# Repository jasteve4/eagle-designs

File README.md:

# eagle-designs
designs for ncsu IEEE Robotics

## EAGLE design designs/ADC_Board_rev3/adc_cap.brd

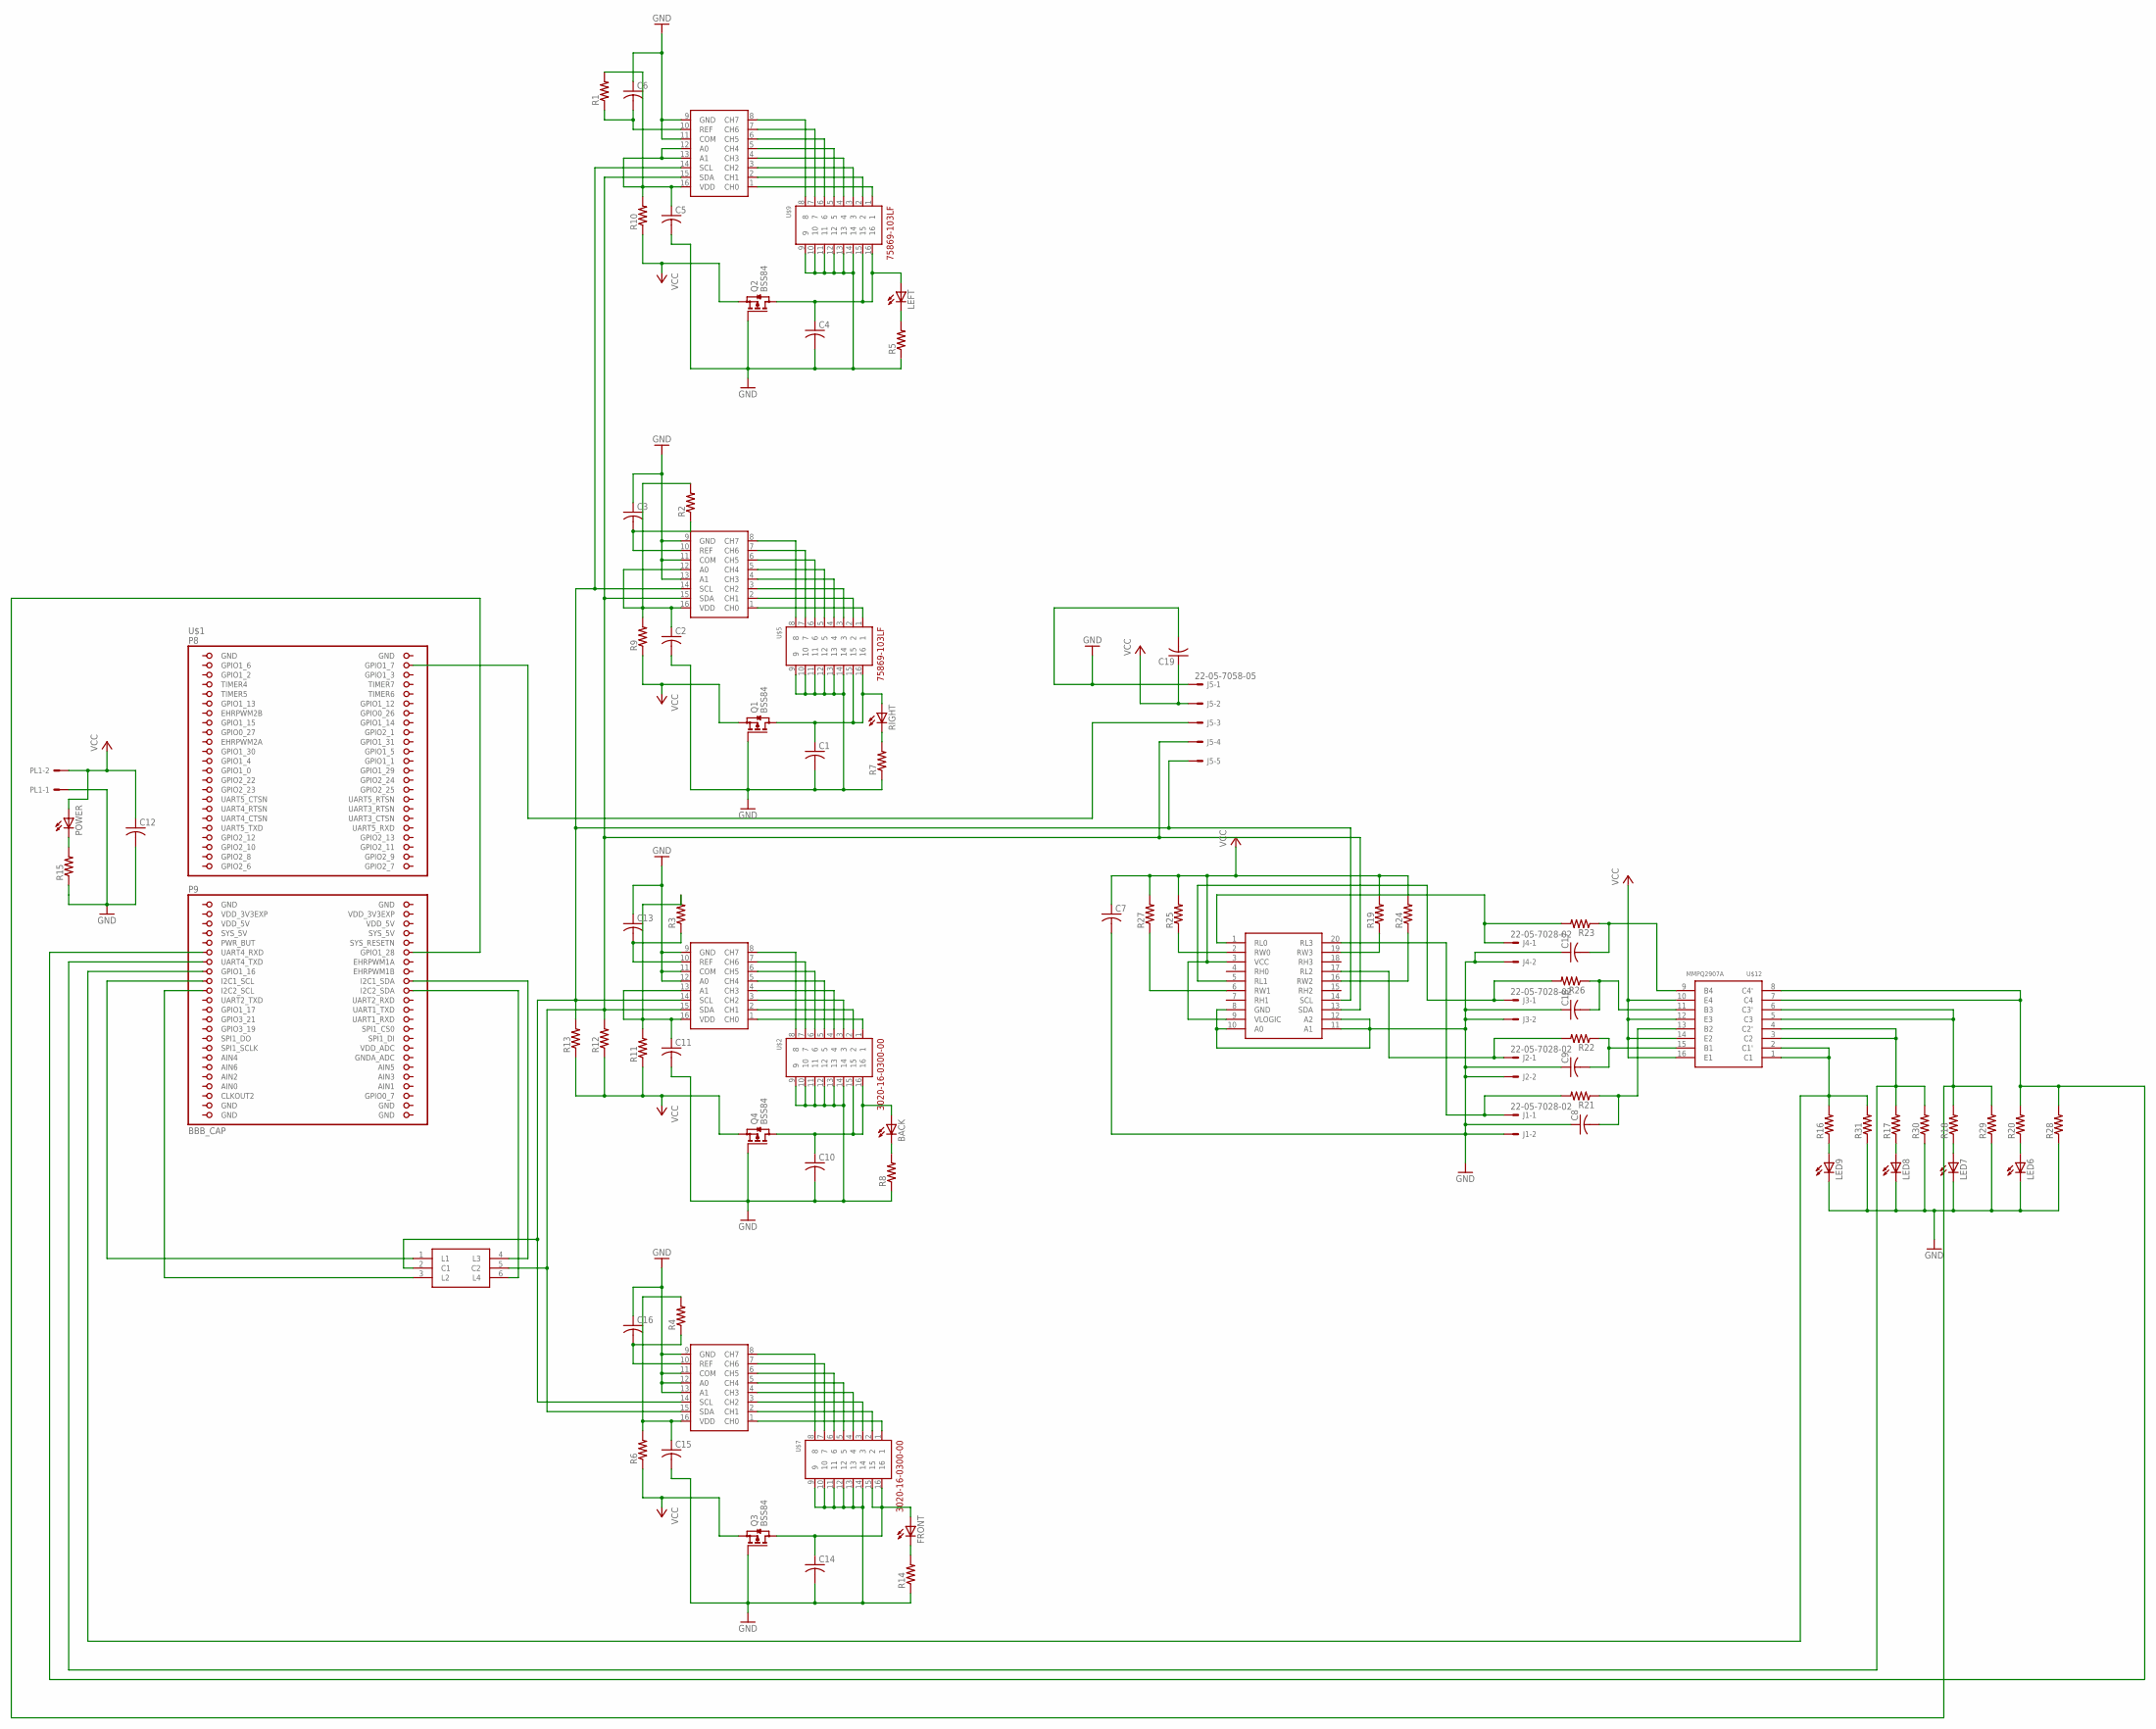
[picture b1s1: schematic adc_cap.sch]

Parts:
BACK: LEDSML1206; SML1206
C1, C2, C3, C4, C5, C6, C7, C8, C9, C10, C11, C13, C14, C15, C16, C17, C18, C19: C-USC1206K; C1206K
C12: C-USC0805; C0805
FRONT: LEDSML1206; SML1206
J1, J2, J3, J4: 22-05-7028-02; 7395-02
J5: 22-05-7058-05; 7395-05
LED6, LED7, LED8, LED9: LEDSML1206; SML1206
LEFT: LEDSML1206; SML1206
PL1: 555X-2H; 5569-2
POWER: LEDSML1206; SML1206
Q1, Q2, Q3, Q4: BSS84; SOT23
R1, R2, R3, R4, R5, R6, R7, R8, R9, R10, R11, R12, R13, R14, R15, R16, R17, R18, R19, R20, R21, R22, R23, R24, R25, R26, R27, R28, R29, R30, R31: R-US_R1206W; R1206W
RIGHT: LEDSML1206; SML1206
U$1: BBB_CAP; BBB
U$2, U$7: 3020-16-0300-00; 8X2_SMD_HEADER
U$3, U$4, U$6, U$8: ADS7830; ADC8_SD
U$5, U$9: 75869-103LF; 8X2_THROUGH_HOLE_HEADER
U$10: CAS-220TB; DPDT_DIP_SWITCH
U$11: ISL23348_SD; TSSOP-20
U$12: MMPQ2907A; SO1C-16

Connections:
AIN0: U$1.P9_39 (AIN0)
GND: C1.2, C2.2, C3.1, C4.2, C5.2, C6.1, C7.2, C8.1, C9.1, C10.2, C11.2, C12.2, C13.1, C14.2, C15.2, C16.1, C17.1, C18.1, C19.2, J1.2, J2.2, J3.2, J4.2, J5.1, LED6.C, LED7.C, LED8.C, LED9.C, PL1.1, Q1.1 (G), Q2.1 (G), Q3.1 (G), Q4.1 (G), R5.1, R7.1, R8.1, R14.1, R28.1, R29.1, R30.1, R31.1, U$1.P8_1 (GND), U$1.P8_2 (GND), U$1.P9_1 (GND), U$1.P9_2 (GND), U$1.P9_43 (GND), U$1.P9_44 (GND), U$1.P9_45 (GND), U$1.P9_46 (GND), U$2.9, U$2.10, U$2.11, U$2.12, U$2.13, U$2.14, U$3.9 (GND), U$3.11 (COM), U$3.12 (A0), U$4.9 (GND), U$4.11 (COM), U$4.13 (A1), U$5.9, U$5.10, U$5.11, U$5.12, U$5.13, U$5.14, U$6.9 (GND), U$6.11 (COM), U$7.9, U$7.10, U$7.11, U$7.12, U$7.13, U$7.14, U$8.9 (GND), U$8.11 (COM), U$8.12 (A0), U$8.13 (A1), U$9.9, U$9.10, U$9.11, U$9.12, U$9.13, U$9.14, U$11.8 (GND), U$11.10 (A0), U$11.11 (A1), U$11.12 (A2)
GND4: R15.1
unnamed: U$2.1, U$3.1 (CH0)
unnamed: J5.4, R12.2, U$3.15 (SDA), U$4.15 (SDA), U$6.15 (SDA), U$8.15 (SDA), U$10.5 (C2), U$11.13 (SDA)
unnamed: U$2.2, U$3.2 (CH1)
unnamed: U$2.3, U$3.3 (CH2)
unnamed: U$2.4, U$3.4 (CH3)
unnamed: U$2.5, U$3.5 (CH4)
unnamed: U$2.6, U$3.6 (CH5)
unnamed: U$2.7, U$3.7 (CH6)
unnamed: U$2.8, U$3.8 (CH7)
unnamed: U$1.P9_18 (I2C1_SDA), U$10.4 (L3)
unnamed: U$1.P9_20 (I2C2_SDA), U$10.6 (L4)
unnamed: C13.2, R3.1, U$3.10 (REF)
unnamed: J5.5, R13.2, U$3.14 (SCL), U$4.14 (SCL), U$6.14 (SCL), U$8.14 (SCL), U$10.2 (C1), U$11.14 (SCL)
unnamed: R19.1, U$11.19 (RW3)
unnamed: U$4.1 (CH0), U$5.1
unnamed: U$4.2 (CH1), U$5.2
unnamed: U$4.3 (CH2), U$5.3
unnamed: U$4.4 (CH3), U$5.4
unnamed: U$4.5 (CH4), U$5.5
unnamed: U$4.6 (CH5), U$5.6
unnamed: U$4.7 (CH6), U$5.7
unnamed: U$4.8 (CH7), U$5.8
unnamed: U$1.P9_17 (I2C1_SCL), U$10.1 (L1)
unnamed: U$1.P9_19 (I2C2_SCL), U$10.3 (L2)
unnamed: C11.1, R3.2, R11.2, U$3.13 (A1), U$3.16 (VDD)
unnamed: C3.2, R2.1, U$4.10 (REF)
unnamed: C4.1, LEFT.A, Q2.3 (D), U$9.15, U$9.16
unnamed: U$6.1 (CH0), U$9.1
unnamed: U$6.2 (CH1), U$9.2
unnamed: U$6.3 (CH2), U$9.3
unnamed: U$6.4 (CH3), U$9.4
unnamed: U$6.5 (CH4), U$9.5
unnamed: U$6.6 (CH5), U$9.6
unnamed: U$6.7 (CH6), U$9.7
unnamed: U$6.8 (CH7), U$9.8
unnamed: R24.1, U$11.16 (RW2)
unnamed: U$7.1, U$8.1 (CH0)
unnamed: C2.1, R2.2, R9.2, U$4.12 (A0), U$4.16 (VDD)
unnamed: C6.2, R1.1, U$6.10 (REF)
unnamed: R25.1, U$11.2 (RW0)
unnamed: U$7.2, U$8.2 (CH1)
unnamed: U$7.3, U$8.3 (CH2)
unnamed: U$7.4, U$8.4 (CH3)
unnamed: U$7.5, U$8.5 (CH4)
unnamed: U$7.6, U$8.6 (CH5)
unnamed: U$7.7, U$8.7 (CH6)
unnamed: U$7.8, U$8.8 (CH7)
unnamed: C5.1, R1.2, R10.2, U$6.12 (A0), U$6.13 (A1), U$6.16 (VDD)
unnamed: LEFT.C, R5.2
unnamed: R27.1, U$11.6 (RW1)
unnamed: C15.1, R4.2, R6.2, U$8.16 (VDD)
unnamed: C16.2, R4.1, U$8.10 (REF)
unnamed: C1.1, Q1.3 (D), RIGHT.A, U$5.15, U$5.16
unnamed: R7.2, RIGHT.C
unnamed: BACK.A, C10.1, Q4.3 (D), U$2.15, U$2.16
unnamed: BACK.C, R8.2
unnamed: C14.1, FRONT.A, Q3.3 (D), U$7.15, U$7.16
unnamed: FRONT.C, R14.2
unnamed: LED8.A, R17.1
unnamed: POWER.C, R15.2
unnamed: J4.1, R23.2, U$11.1 (RL0)
unnamed: J3.1, R26.2, U$11.5 (RL1)
unnamed: J2.1, R22.2, U$11.17 (RL2)
unnamed: J1.1, R21.2, U$11.20 (RL3)
unnamed: LED9.A, R16.1
unnamed: LED7.A, R18.1
unnamed: LED6.A, R20.1
unnamed: C17.2, R23.1, U$12.9 (B4)
unnamed: C18.2, R26.1, U$12.11 (B3)
unnamed: C9.2, R22.1, U$12.15 (B1)
unnamed: C8.2, R21.1, U$12.13 (B2)
unnamed: J5.3, U$1.P8_4 (GPIO1_7)
unnamed: R17.2, R30.2, U$1.P9_13 (UART4_TXD), U$12.3 (C2), U$12.4 (C2')
unnamed: R20.2, R28.2, U$1.P9_11 (UART4_RXD), U$12.7 (C4), U$12.8 (C4')
unnamed: R18.2, R29.2, U$1.P9_12 (GPIO1_28), U$12.5 (C3), U$12.6 (C3')
unnamed: R16.2, R31.2, U$1.P9_15 (GPIO1_16), U$12.1 (C1), U$12.2 (C1')
SYS_5V: U$1.P9_7 (SYS_5V)
VCC: C7.1, C12.1, C19.1, J5.2, PL1.2, POWER.A, Q1.2 (S), Q2.2 (S), Q3.2 (S), Q4.2 (S), R6.1, R9.1, R10.1, R11.1, R12.1, R13.1, R19.2, R24.2, R25.2, R27.2, U$11.3 (VCC), U$11.9 (VLOGIC), U$12.10 (E4), U$12.12 (E3), U$12.14 (E2), U$12.16 (E1)
VDD_3V3EXP: U$1.P9_3 (VDD_3V3EXP), U$1.P9_4 (VDD_3V3EXP)
VDD_5V: U$1.P9_5 (VDD_5V), U$1.P9_6 (VDD_5V)

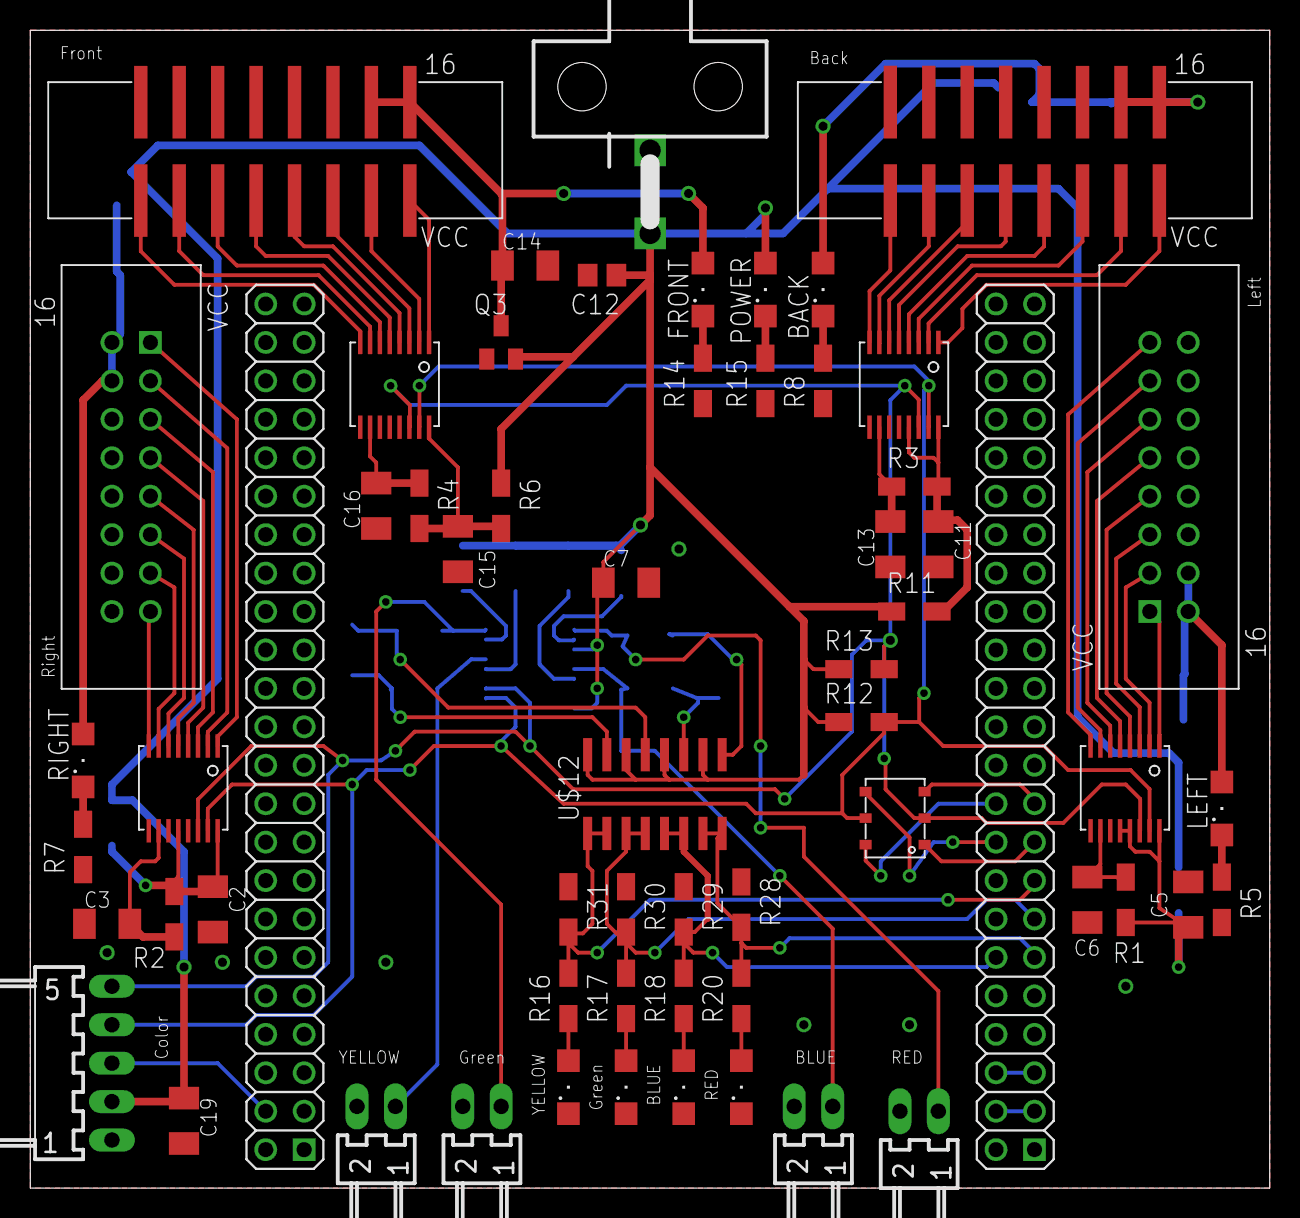
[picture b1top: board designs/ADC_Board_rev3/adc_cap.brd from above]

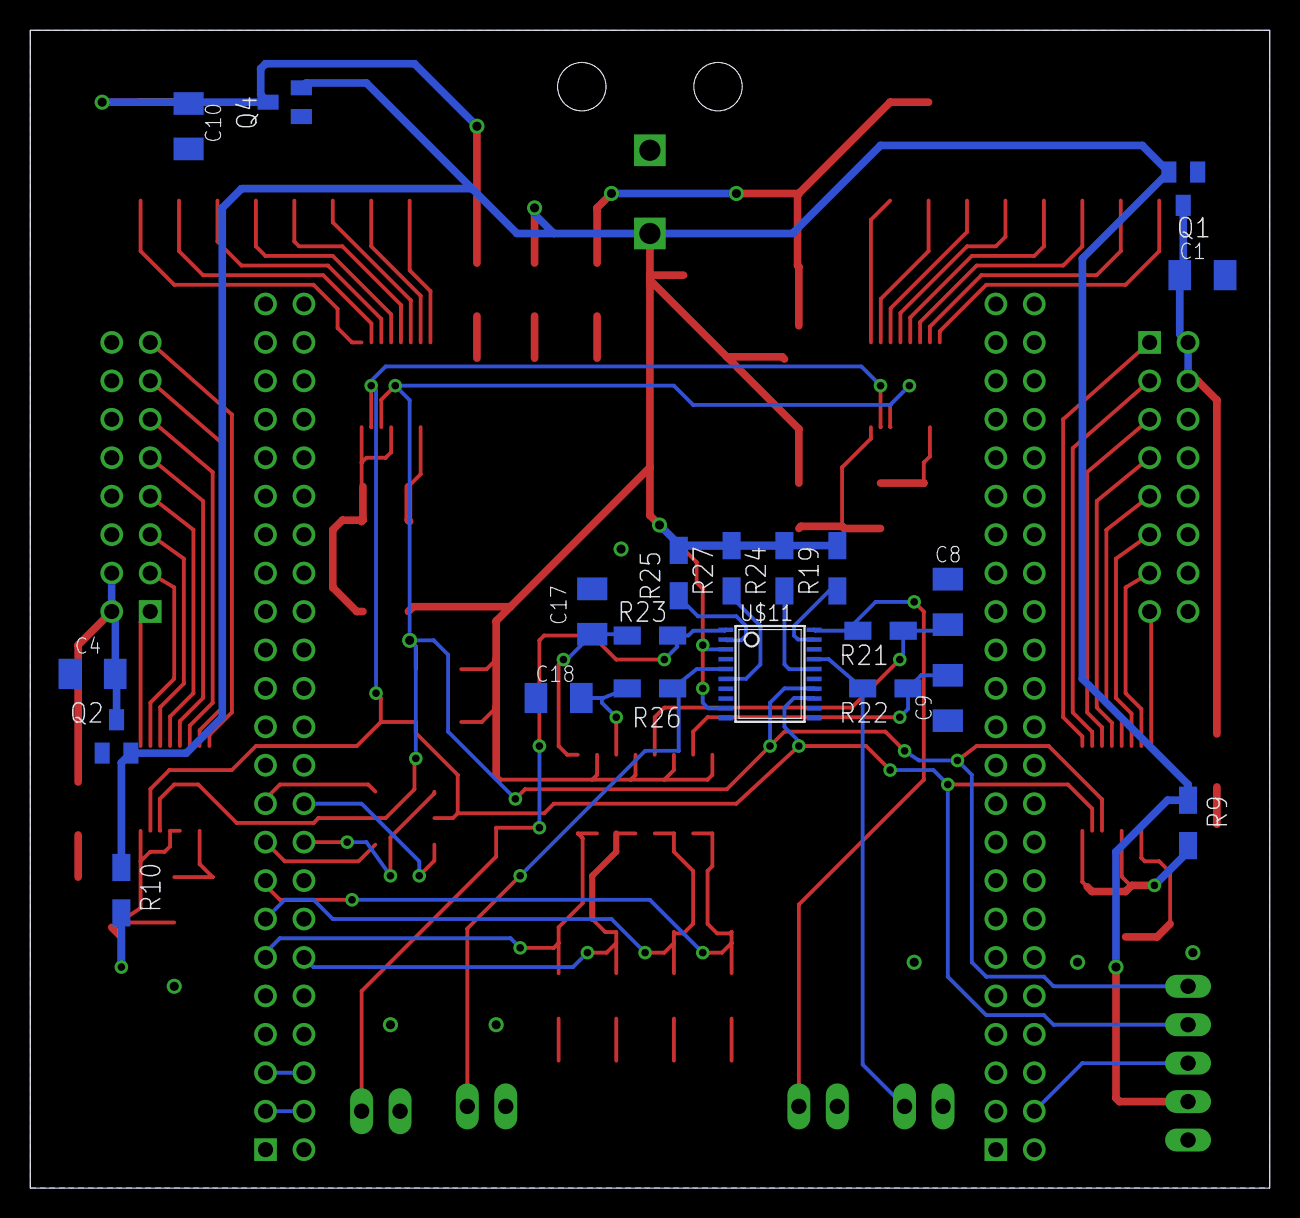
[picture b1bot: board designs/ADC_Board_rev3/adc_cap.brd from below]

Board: 2 copper layers, 81.9 x 76.5 mm, 81 parts (21 on the bottom side), 80 nets.

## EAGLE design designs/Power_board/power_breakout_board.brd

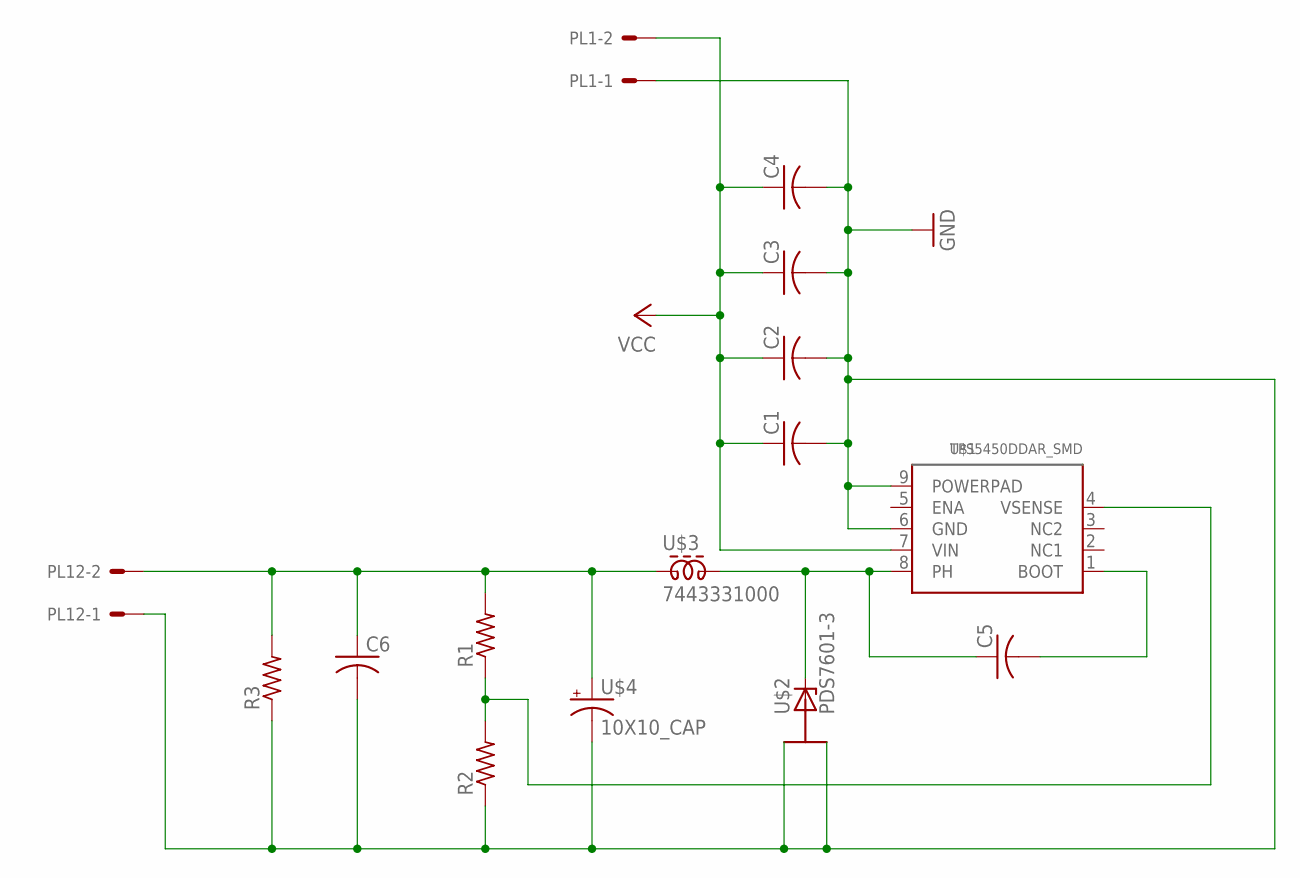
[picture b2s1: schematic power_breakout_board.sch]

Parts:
C1, C2, C3, C4, C6: C-USC1206K; C1206K
C5: C-USC0805K; C0805K
PL1, PL12: 555X-2H; 5569-2
R1, R2, R3: R-US_R1206; R1206
U$1: TPS5450DDAR_SMD; SO-POWERPAD
U$2: PDS7601-3; POWERDI-5_SMD
U$3: 7443331000; 7443331000_SMD
U$4: 10X10_CAP; 10X10_CAP_SMD

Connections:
GND: C1.2, C2.2, C3.2, C4.2, C6.2, PL1.1, PL12.1, R2.1, R3.1, U$1.6 (GND), U$1.9 (POWERPAD), U$2.LEFT, U$2.RIGHT, U$4.-
unnamed: C5.2, U$1.1 (BOOT)
unnamed: R1.1, R2.2, U$1.4 (VSENSE)
PH: C5.1, U$1.8 (PH), U$2.HEAT, U$3.P2 (2)
VCC: C1.1, C2.1, C3.1, C4.1, PL1.2, U$1.7 (VIN)
VOUT: C6.1, PL12.2, R1.2, R3.2, U$3.P1 (1), U$4.+

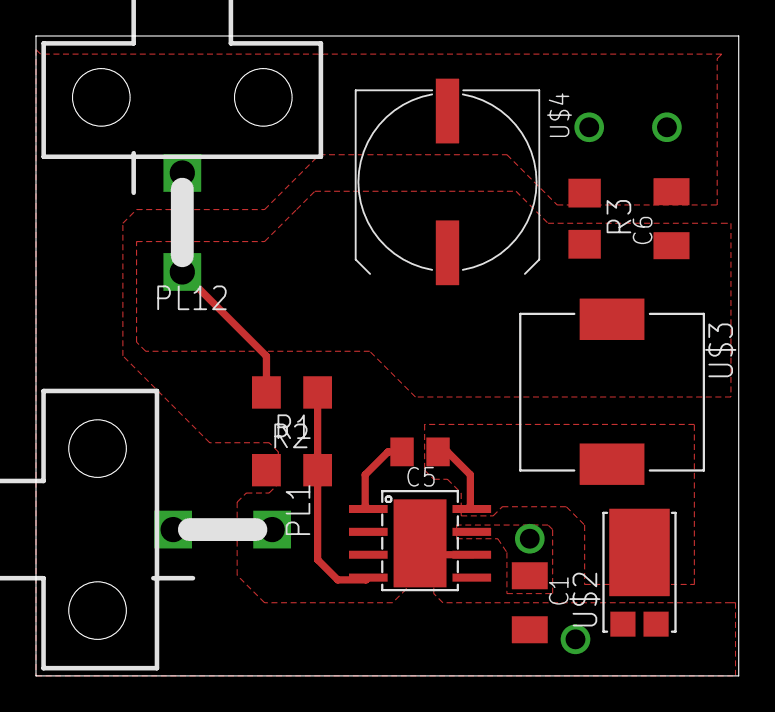
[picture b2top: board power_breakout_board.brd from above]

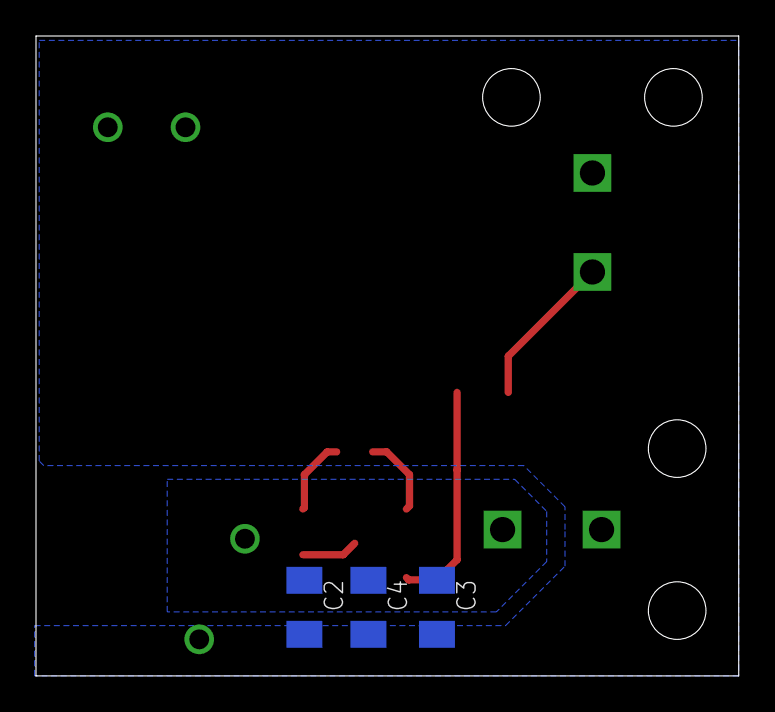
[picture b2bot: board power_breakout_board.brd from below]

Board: 2 copper layers, 39.0 x 35.5 mm, 15 parts (3 on the bottom side), 6 nets.

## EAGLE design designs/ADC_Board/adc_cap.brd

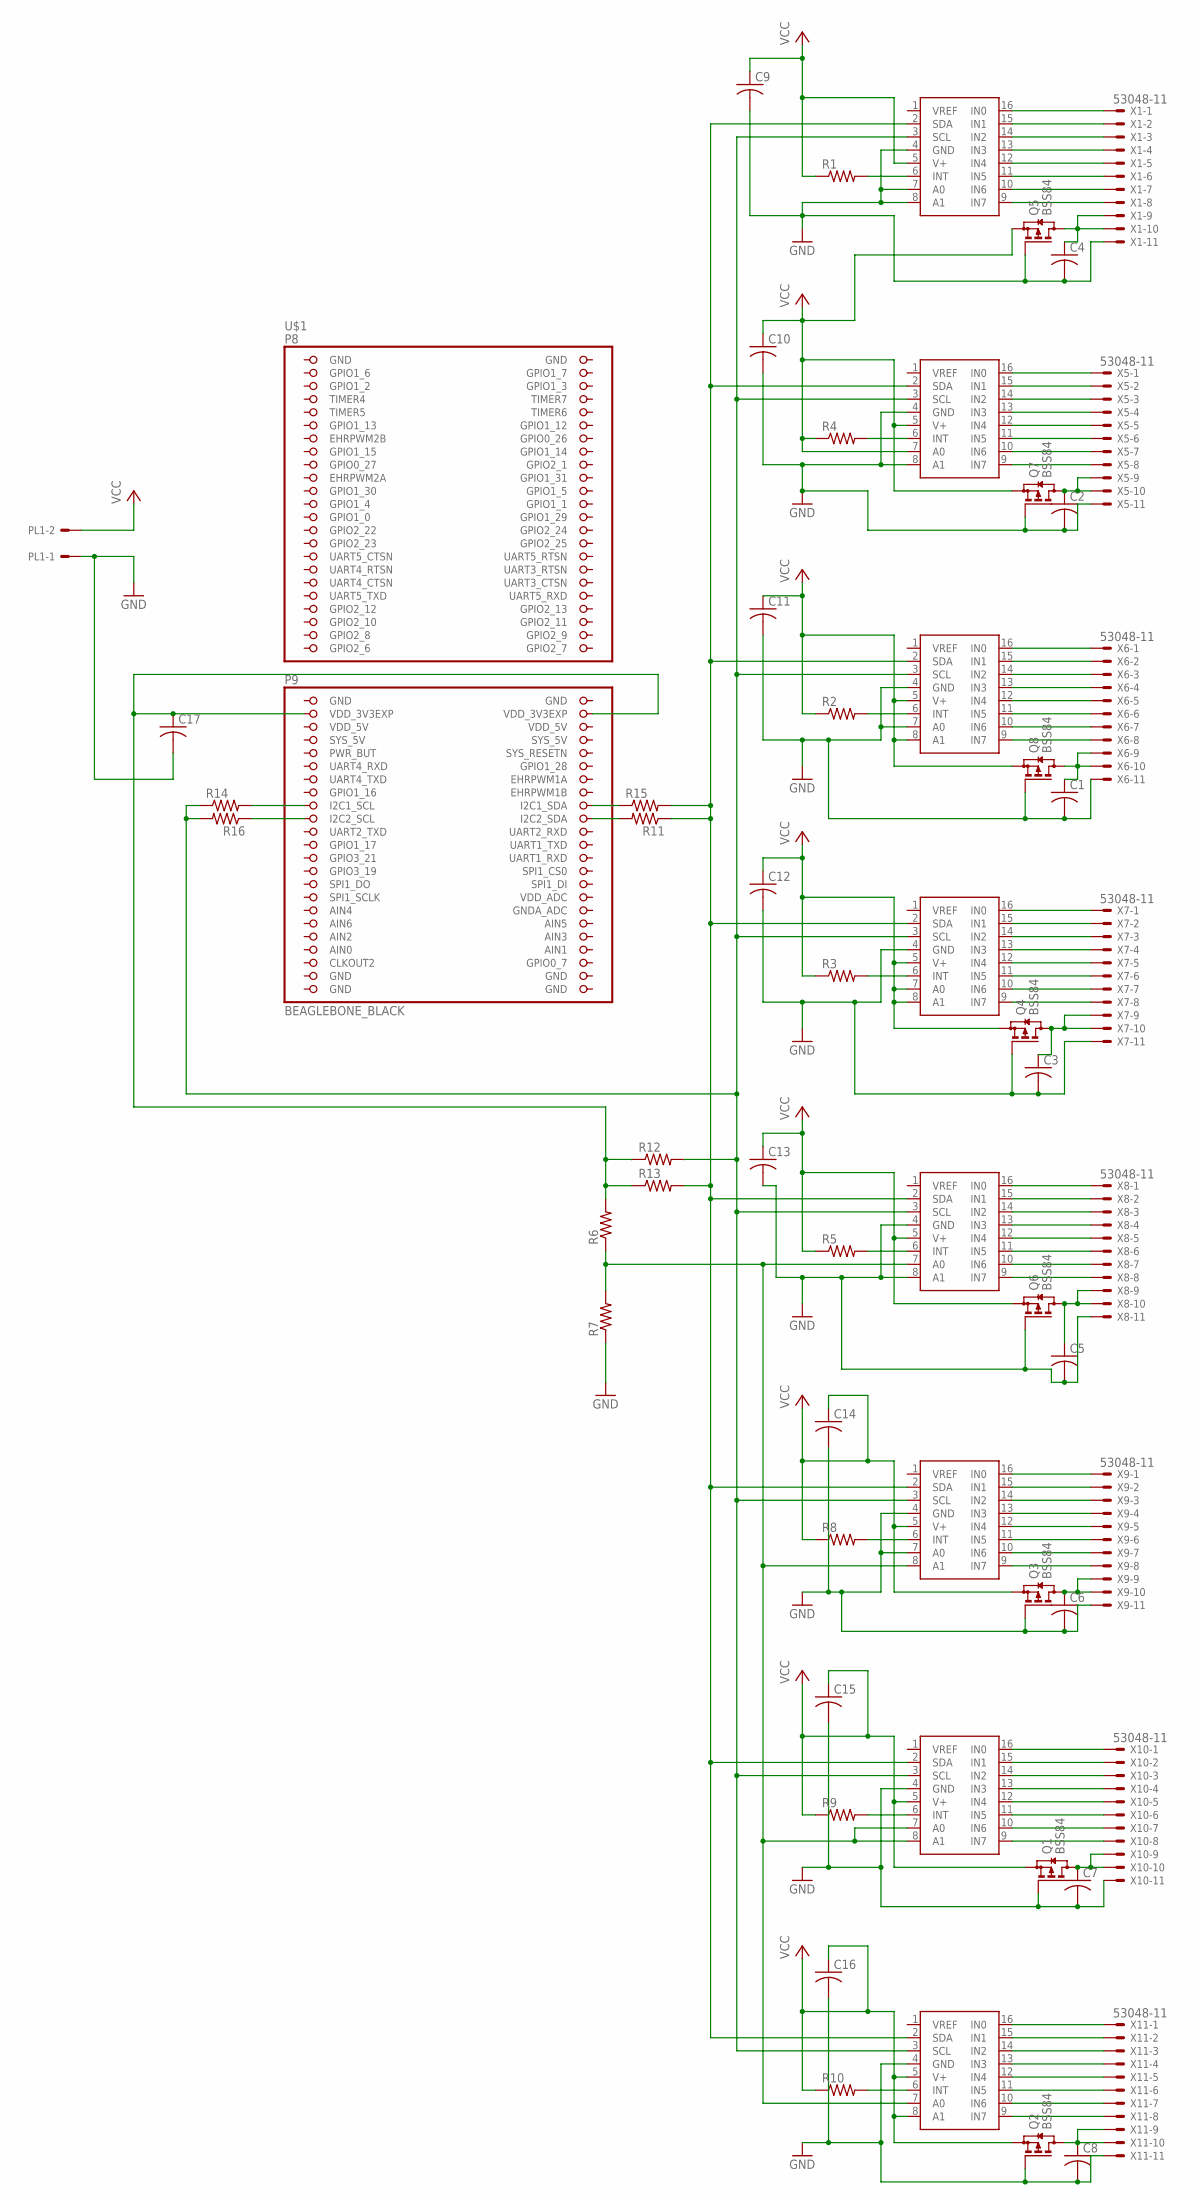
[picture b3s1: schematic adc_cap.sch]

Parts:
C1, C2, C3, C4, C5, C6, C7, C8, C9, C10, C11, C12, C13, C14, C15, C16, C17: C-USC0805; C0805
PL1: 555X-2H; 5569-2
Q1, Q2, Q3, Q4, Q5, Q6, Q7, Q8: BSS84; SOT23
R1, R2, R3, R4, R5, R6, R7, R8, R9, R10, R11, R12, R13, R14, R15, R16: R-US_R0805; R0805
U$1: BEAGLEBONE_BLACK; BEAGEBONE
U$2, U$3, U$4, U$5, U$6, U$7, U$8, U$9: ADC128D818; ADC12_SD
X1, X5, X6, X7, X8, X9, X10, X11: 53048-11

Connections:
AIN0: U$1.146 (AIN0)
GND: C1.2, C2.2, C3.2, C4.2, C5.2, C6.2, C7.2, C8.2, C9.2, C10.2, C11.2, C12.2, C13.2, C14.2, C15.2, C16.2, C17.2, PL1.1, Q1.1 (G), Q2.1 (G), Q3.1 (G), Q4.1 (G), Q5.1 (G), Q6.1 (G), Q7.1 (G), Q8.1 (G), R7.1, U$1.137 (GND), U$1.138 (GND), U$1.139 (GND), U$1.140 (GND), U$1.141 (GND), U$1.142 (GND), U$1.183 (GND), U$1.184 (GND), U$2.4 (GND), U$2.8 (A1), U$3.4 (GND), U$3.7 (A0), U$3.8 (A1), U$4.4 (GND), U$4.7 (A0), U$5.4 (GND), U$6.4 (GND), U$6.8 (A1), U$7.4 (GND), U$7.7 (A0), U$8.4 (GND), U$9.4 (GND), X1.11, X5.11, X6.11, X7.11, X8.11, X9.11, X10.11, X11.11
unnamed: U$3.16 (IN0), X1.1
unnamed: U$3.15 (IN1), X1.2
unnamed: U$3.14 (IN2), X1.3
unnamed: U$3.13 (IN3), X1.4
unnamed: U$3.12 (IN4), X1.5
unnamed: U$3.11 (IN5), X1.6
unnamed: U$3.10 (IN6), X1.7
unnamed: U$3.9 (IN7), X1.8
unnamed: U$9.16 (IN0), X11.1
unnamed: U$9.15 (IN1), X11.2
unnamed: U$9.14 (IN2), X11.3
unnamed: U$9.13 (IN3), X11.4
unnamed: U$9.12 (IN4), X11.5
unnamed: U$9.11 (IN5), X11.6
unnamed: U$9.10 (IN6), X11.7
unnamed: U$9.9 (IN7), X11.8
unnamed: U$8.16 (IN0), X10.1
unnamed: U$8.15 (IN1), X10.2
unnamed: R4.2, U$2.6 (INT)
unnamed: U$8.14 (IN2), X10.3
unnamed: U$8.13 (IN3), X10.4
unnamed: U$8.12 (IN4), X10.5
unnamed: U$8.11 (IN5), X10.6
unnamed: U$8.10 (IN6), X10.7
unnamed: U$8.9 (IN7), X10.8
unnamed: R2.2, U$4.6 (INT)
unnamed: U$7.16 (IN0), X9.1
unnamed: U$7.15 (IN1), X9.2
unnamed: U$7.14 (IN2), X9.3
unnamed: U$7.13 (IN3), X9.4
unnamed: U$7.12 (IN4), X9.5
unnamed: U$7.11 (IN5), X9.6
unnamed: U$7.10 (IN6), X9.7
unnamed: U$7.9 (IN7), X9.8
unnamed: R3.2, U$5.6 (INT)
unnamed: U$6.16 (IN0), X8.1
unnamed: U$6.15 (IN1), X8.2
unnamed: U$6.14 (IN2), X8.3
unnamed: U$6.13 (IN3), X8.4
unnamed: U$6.12 (IN4), X8.5
unnamed: U$6.11 (IN5), X8.6
unnamed: U$6.10 (IN6), X8.7
unnamed: U$6.9 (IN7), X8.8
unnamed: R5.2, U$6.6 (INT)
unnamed: R6.1, R7.2, U$6.7 (A0), U$7.8 (A1), U$8.7 (A0), U$8.8 (A1), U$9.7 (A0)
unnamed: U$5.16 (IN0), X7.1
unnamed: U$5.15 (IN1), X7.2
unnamed: U$5.14 (IN2), X7.3
unnamed: U$5.13 (IN3), X7.4
unnamed: U$5.12 (IN4), X7.5
unnamed: U$5.11 (IN5), X7.6
unnamed: U$5.10 (IN6), X7.7
unnamed: U$5.9 (IN7), X7.8
unnamed: R8.2, U$7.6 (INT)
unnamed: R12.2, R14.1, R16.2, U$2.3 (SCL), U$3.3 (SCL), U$4.3 (SCL), U$5.3 (SCL), U$6.3 (SCL), U$7.3 (SCL), U$8.3 (SCL), U$9.3 (SCL)
unnamed: U$4.16 (IN0), X6.1
unnamed: U$4.15 (IN1), X6.2
unnamed: U$4.14 (IN2), X6.3
unnamed: U$4.13 (IN3), X6.4
unnamed: U$4.12 (IN4), X6.5
unnamed: U$4.11 (IN5), X6.6
unnamed: U$4.10 (IN6), X6.7
unnamed: U$4.9 (IN7), X6.8
unnamed: R9.2, U$8.6 (INT)
unnamed: U$2.16 (IN0), X5.1
unnamed: U$2.15 (IN1), X5.2
unnamed: R1.2, U$3.6 (INT)
unnamed: U$2.14 (IN2), X5.3
unnamed: U$2.13 (IN3), X5.4
unnamed: U$2.12 (IN4), X5.5
unnamed: U$2.11 (IN5), X5.6
unnamed: U$2.10 (IN6), X5.7
unnamed: U$2.9 (IN7), X5.8
unnamed: R10.2, U$9.6 (INT)
unnamed: C4.1, Q5.3 (D), X1.9, X1.10
unnamed: C3.1, Q4.3 (D), X7.9, X7.10
unnamed: C1.1, Q8.3 (D), X6.9, X6.10
unnamed: C7.1, Q1.3 (D), X10.9, X10.10
unnamed: C2.1, Q7.3 (D), X5.9, X5.10
unnamed: R11.2, U$1.167 (I2C2_SDA)
unnamed: R15.1, U$1.165 (I2C1_SDA)
unnamed: C5.1, Q6.3 (D), X8.9, X8.10
unnamed: C8.1, Q2.3 (D), X11.9, X11.10
unnamed: R11.1, R13.2, R15.2, U$2.2 (SDA), U$3.2 (SDA), U$4.2 (SDA), U$5.2 (SDA), U$6.2 (SDA), U$7.2 (SDA), U$8.2 (SDA), U$9.2 (SDA)
unnamed: R14.2, U$1.168 (I2C1_SCL)
unnamed: R16.1, U$1.166 (I2C2_SCL)
unnamed: C6.1, Q3.3 (D), X9.9, X9.10
unnamed: C17.1, R6.2, R12.1, R13.1, U$1.181 (VDD_3V3EXP), U$1.182 (VDD_3V3EXP)
SYS_5V: U$1.178 (SYS_5V)
VCC: C9.1, C10.1, C11.1, C12.1, C13.1, C14.1, C15.1, C16.1, PL1.2, Q1.2 (S), Q2.2 (S), Q3.2 (S), Q4.2 (S), Q5.2 (S), Q6.2 (S), Q7.2 (S), Q8.2 (S), R1.1, R2.1, R3.1, R4.1, R5.1, R8.1, R9.1, R10.1, U$2.5 (V+), U$2.7 (A0), U$3.5 (V+), U$4.5 (V+), U$4.8 (A1), U$5.5 (V+), U$5.7 (A0), U$5.8 (A1), U$6.5 (V+), U$7.5 (V+), U$8.5 (V+), U$9.5 (V+), U$9.8 (A1)
VDD_5V: U$1.179 (VDD_5V), U$1.180 (VDD_5V)

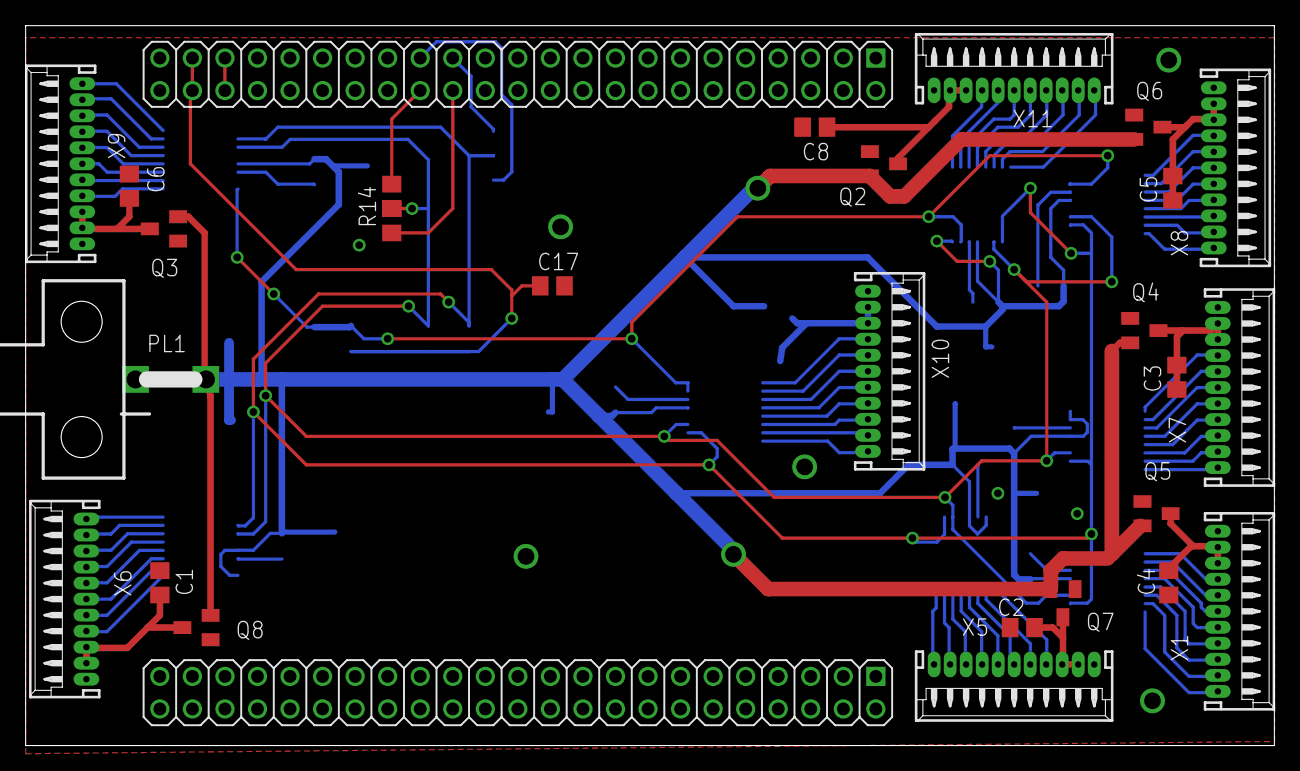
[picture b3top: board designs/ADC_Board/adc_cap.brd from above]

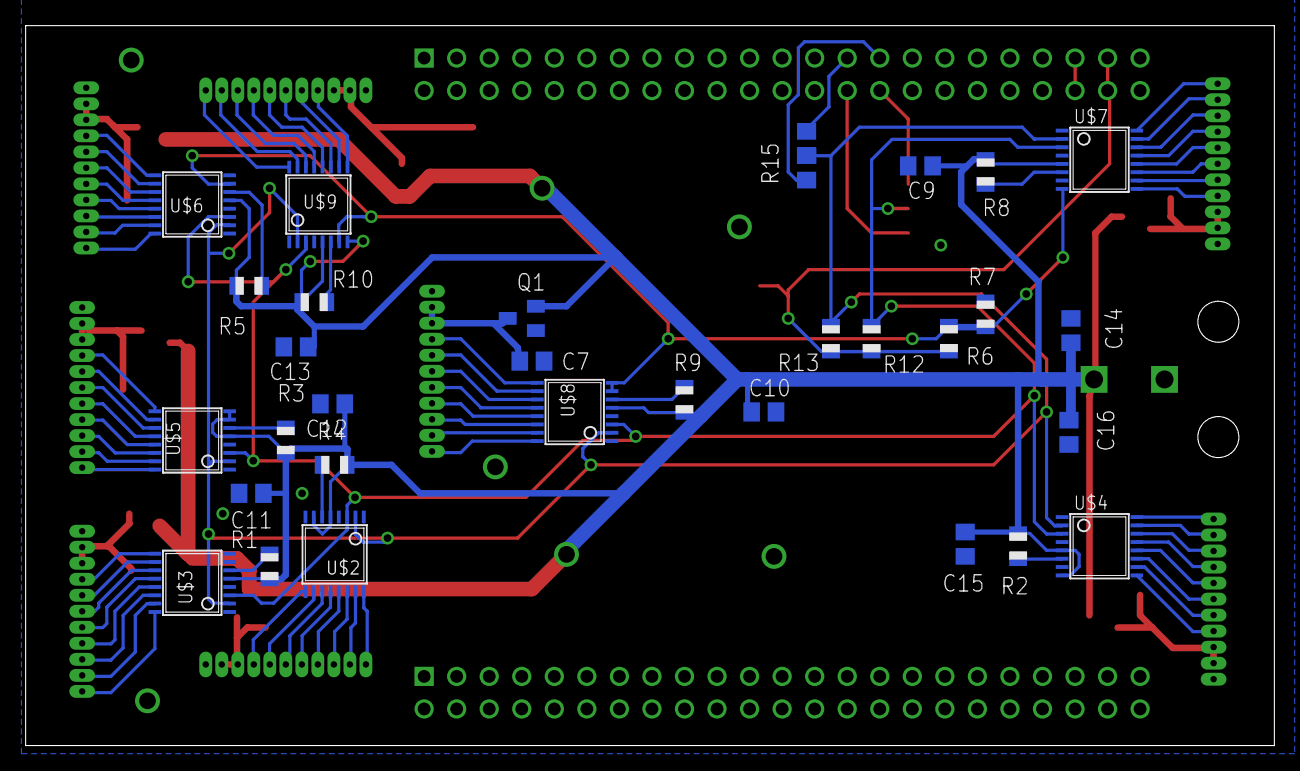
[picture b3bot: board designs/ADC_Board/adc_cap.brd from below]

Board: 2 copper layers, 97.5 x 56.2 mm, 59 parts (32 on the bottom side), 91 nets.
